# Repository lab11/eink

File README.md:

# E-Ink
This is a BLE-controlled e-ink display built off of the nrf51822.

## Software
The nrf software can be found in ``` /software/nrf5x-base/apps/eink-advanced/ ```

## Summon App
[Summon](https://github.com/lab11/summon) is a UI application for BLE devices. Rather than requiring every user to install a new app for every BLE device, Summon allows BLE devices to point to their own HTML/JS based interface and loads it in a single application. Eink supports the summon architecture and provides a Summon application.

## Hardware
The hardware is built on top of the nrf51822. A full parts list can be found in the ``` /hardware ``` directory, along with pcb and case designs.

## API

| Characteristic name | uuid                                 | Data Type                      | Range   |
| ------------------- | ------------------------------------ | ------------------------------ | --------
| service             | e528a44a-ff4f-3089-d44f-7cb505aba641 | None                           |         |
| text                | e528a410-ff4f-3089-d44f-7cb505aba641 | 20 byte packets up to 60 bytes |         |
| x coordinate        | e528a411-ff4f-3089-d44f-7cb505aba641 | uint16_t                       | 0 - 400 |
| y coordinate        | e528a412-ff4f-3089-d44f-7cb505aba641 | uint16_t                       | 0 - 300 |
| scale               | e528a413-ff4f-3089-d44f-7cb505aba641 | uint8_t                        | 0 - 10  |
| qrcode              | e528a414-ff4f-3089-d44f-7cb505aba641 | 20 bytes                       |         |
| control             | e528a415-ff4f-3089-d44f-7cb505aba641 | uint8_t                        |         |

#### Text
~~1. Break your text up into 19-byte packets.
2. Create an array of these packets.
3. For each packet, make the first byte equal to its distance from the last packet (the first byte of the first packet would be chunks.length - 1, the first byte of the last packet will be 0).
4. The remaining bytes will be the text packet.~~

**You can only write 18 characters at a time.**

#### Control
Writing 1 to control will refresh the display to show changes that have been made.
Writing 2 to control will clear the screen.

### Example

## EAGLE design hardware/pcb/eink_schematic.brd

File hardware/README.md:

#Parts

| Name            | Price  | Link                                                                                                                |
| --------------- | ------ | ------------------------------------------------------------------------------------------------------------------- |
| Eink Display    | $66.00 | http://www.digikey.com/product-detail/en/ST044AS182/ST044AS182-ND/4898786                                           |
| Female headers  | $00.94 | http://www.digikey.com/product-detail/en/sullins-connector-solutions/PPTC101LGBN-RC/S5446-ND/775904                 |
| Inductor        | $00.48 | http://www.digikey.com/product-detail/en/murata-electronics-north-america/LQH43CN100K03L/490-2519-1-ND/599992       |
| 10uF capacitor  | $00.12 | http://www.digikey.com/product-detail/en/murata-electronics-north-america/GRM155R60G106ME44D/490-10693-1-ND/5251412 |
| 2.2uf capacitor | $00.12 | http://www.digikey.com/product-detail/en/murata-electronics-north-america/GRM188R61C225KE15D/490-3296-1-ND/702837   |
| Max6326         | $03.11 | http://www.digikey.com/product-detail/en/maxim-integrated/MAX6326UR29-T/MAX6326UR29-TCT-ND/2234432                  |
| Mosfet          | $00.39 | http://www.digikey.com/product-detail/en/fairchild-semiconductor/FDN340P/FDN340PCT-ND/965604                        |
| Diode           | $00.38 | http://www.digikey.com/product-detail/en/fairchild-semiconductor/SS15FA/SS15FACT-ND/5892131                         |
| Barrel Jack     | $01.89 | http://www.digikey.com/product-detail/en/cui-inc/PJ-002AH-SMT-TR/CP-002AHPJCT-ND/669692                             |

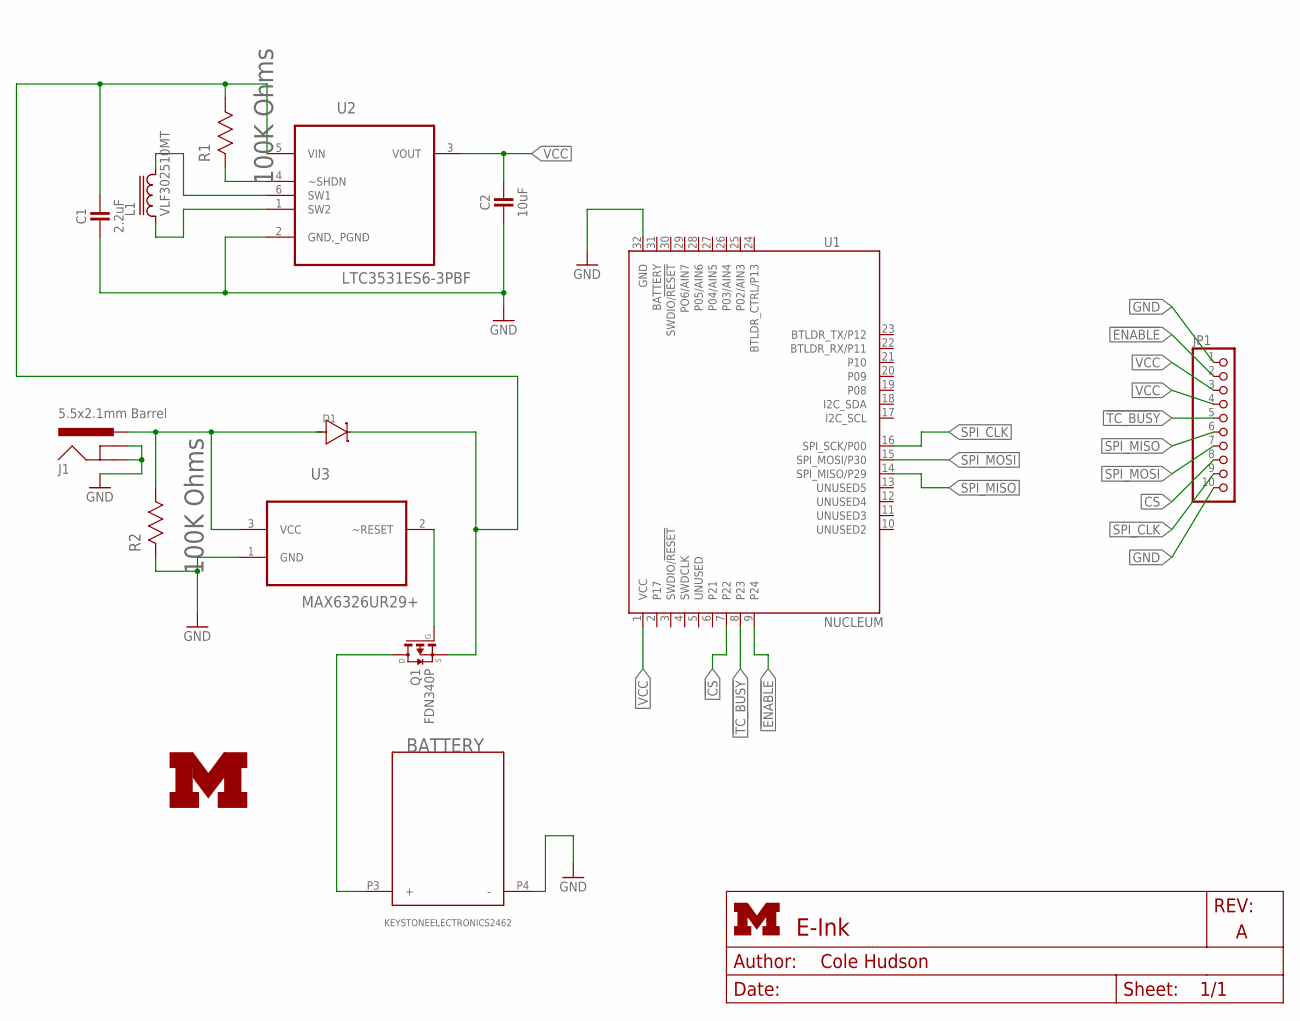
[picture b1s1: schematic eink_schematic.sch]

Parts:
BATTERY: KEYSTONEELECTRONICS2462; DIGIKEY 36-2462-ND
C1: 2.2uF; 0402_CAP; DIGIKEY 490-3296-1-ND
C2: 10uF; 0402_CAP; DIGIKEY 490-10693-1-ND
D1: DIODE[SCHOTKY]-SOD123W; SOD123W; DIGIKEY SS15FACT-ND
J1: 5.5x2.1mm Barrel; POWER_JACK_SMD; DIGIKEY CP-002AHPJCT-ND
JP1: PINHD-1X10/90; 1X10/90; DIGIKEY S5446-ND
L1: VLF302510MT; DIGIKEY 445-6775-1-ND
LOGO1: UMICH_SOLID_LARGE; UMICH_SOLID_350MIL
Q1: FDN340P; SSOT-3; DIGIKEY FDN340PCT-ND
R1: 100K Ohms; RESC1608X60N; DIGIKEY 311-100KGRCT-ND
R2: 100K Ohms; RESC1608X60N
U1: NUCLEUM
U2: LTC3531ES6-3PBF; SOT95P280X100-6N; DIGIKEY LTC3531ES6-3.3#TRMPBFCT-ND
U3: MAX6326UR29+; SOT95P228X119-3N; DIGIKEY MAX6326UR29+TCT-ND

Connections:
!CS: JP1.8, U1.7 (P22)
!ENABLE: JP1.2, U1.9 (P24)
!SHDN: R1.2 (R2), U2.4 (~SHDN)
!TC_BUSY: JP1.5, U1.8 (P23)
GND: BATTERY.P4 (-), C1.2, C2.2, J1.GND (GNDBREAK), J1.P$4 (GND), JP1.1, JP1.10, R2.2 (R2), U1.32 (GND), U2.2 (GND,_PGND), U3.1 (GND)
unnamed: Q1.1 (G), U3.2 (~RESET)
unnamed: D1.P$1 (1), J1.VIN0 (PWR), R2.1 (R1), U3.3 (VCC)
unnamed: C1.1, D1.P$2 (2), Q1.2 (S), R1.1 (R1), U2.5 (VIN)
unnamed: BATTERY.P3 (+), Q1.3 (D)
SPI_CLK: JP1.9, U1.16 (SPI_SCK/P00)
SPI_MISO: JP1.6, U1.14 (SPI_MISO/P29)
SPI_MOSI: JP1.7, U1.15 (SPI_MOSI/P30)
SW1: L1.2, U2.6 (SW1)
SW2: L1.1, U2.1 (SW2)
VCC: C2.1, JP1.3, JP1.4, U1.1 (VCC), U2.3 (VOUT)

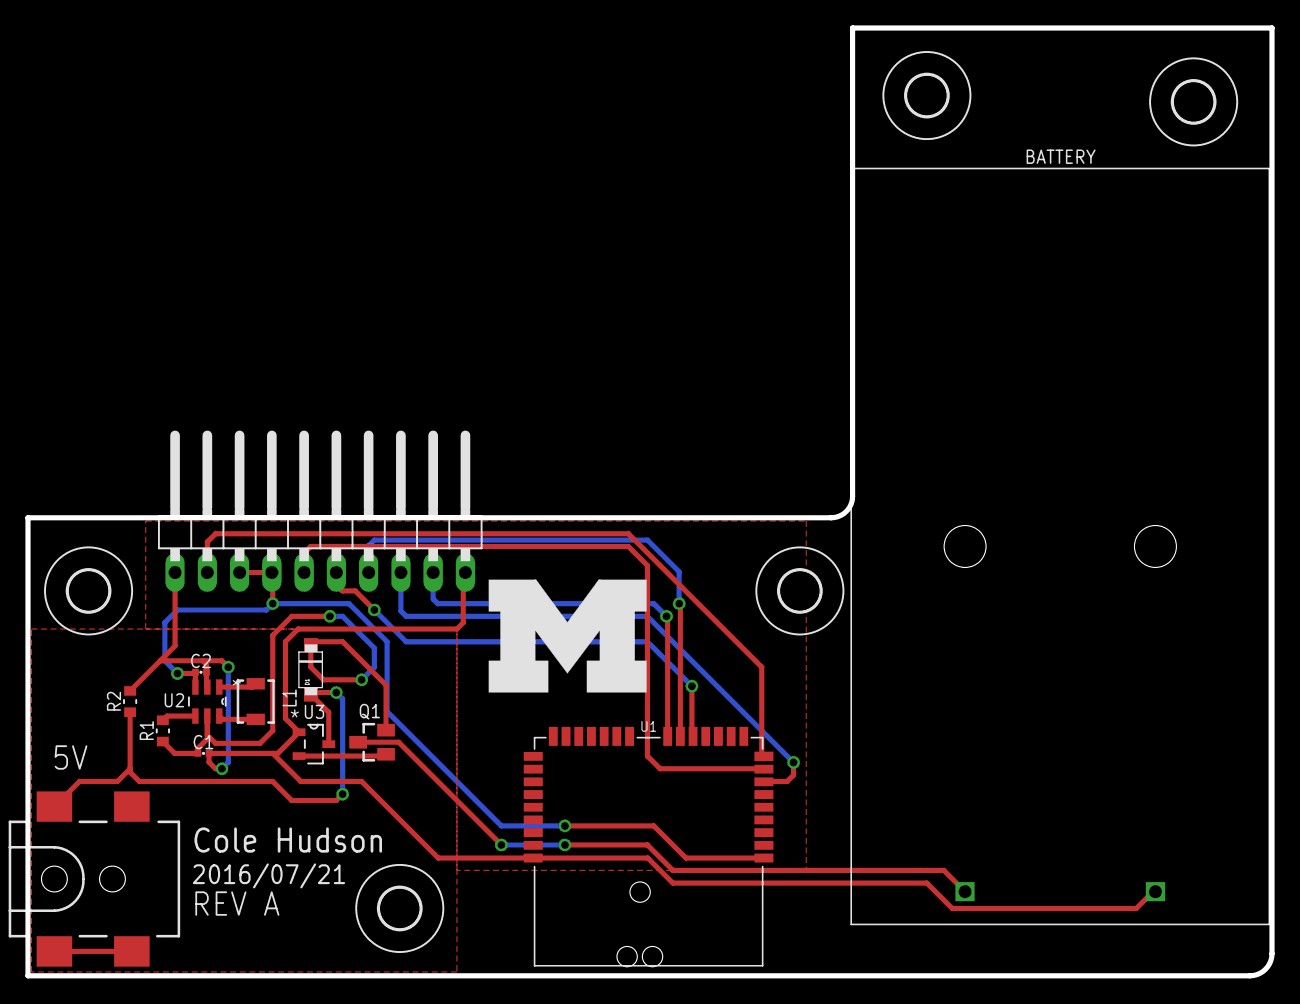
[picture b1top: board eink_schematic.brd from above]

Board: 2 copper layers, 97.9 x 74.6 mm, 19 parts (0 on the bottom side), 15 nets.

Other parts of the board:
U$1, U$2, U$3, U$4, U$5: 3,2

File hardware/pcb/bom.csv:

Qty,Value,Device,Package,Parts,Description,DIGIKEY,MPN,OC_FARNELL,OC_NEWARK,PACKAGE,PROD_ID,SF_ID,SUPPLIER,TOLERANCE,VALUE,WATTAGE
1,,DIODE[SCHOTKY]-SOD123W,SOD123W,D1,,SS15FACT-ND,,,,,,,,,,
1,,PINHD-1X10/90,1X10/90,JP1,PIN HEADER,S5446-ND,,,,,,,,,,
1,100K Ohms,RC0603JR-07100KL,RESC1608X60N,R1,"RESISTOR, 0603",311-100KGRCT-ND,RC0603JR-07100KL,9233628,98K7287,,,,Yageo,±5%,100K Ohms,1/10 W
1,100K Ohms,RC0603JR-07100KL,RESC1608X60N,R2,"RESISTOR, 0603",,RC0603JR-07100KL,9233628,98K7287,,,,Yageo,±5%,100K Ohms,1/10 W
1,10uF,CAPACITOR,0402_CAP,C2,0402 Capacitor,490-10693-1-ND,,,,,,,,,,
1,2.2uF,CAPACITOR,0402_CAP,C1,0402 Capacitor,490-3296-1-ND,,,,,,,,,,
1,5.5x2.1mm Barrel,POWER_JACKSMD,POWER_JACK_SMD,J1,Power Jack,CP-002AHPJCT-ND,,,,,CONN-08106,PRT-12748,,,5.5x2.1mm Barrel,
1,FDN340P,FDN340P,SSOT-3,Q1,P-Channel MOSFET,FDN340PCT-ND,,,,,,,,,,
1,KEYSTONEELECTRONICS2462,KEYSTONEELECTRONICS2462,KEYSTONEELECTRONICS2462,BATTERY,,36-2462-ND,,,,,,,,,,
1,LTC3531ES6-3PBF,LTC3531ES6-3PBF,SOT95P280X100-6N,U2,DC/DC Converters,LTC3531ES6-3.3#TRMPBFCT-ND,LTC3531ES6-3#PBF,-,46P4583,TSOT-23-6,,,Linear Technology,,,
1,MAX6326UR29+,MAX6326UR29+,SOT95P228X119-3N,U3,"3-Pin, Ultra-Low-Power SC70/SOT ìP Reset Circuits",MAX6326UR29+TCT-ND,MAX6326UR29+,9723951,-,SOT-23-3,,,Maxim,,,
1,NUCLEUM,NUCLEUM,NUCLEUM,U1,Nucleum sensorboard prototyping module.,,,,,,,,,,,
1,UMICH_SOLID_LARGE,UMICH_SOLID_LARGE,UMICH_SOLID_350MIL,LOGO1,,,,,,,,,,,,
1,VLF302510MT,VLF302510MT,VLF302510MT,L1,POWER INDUCTOR,445-6775-1-ND,,,,,,,,,,

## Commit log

2016-06-28 Added base summon app
2016-06-28 Added nrf5x-base submodule
2016-06-29 Added readme for summon
2016-06-29 Hopefully fixed summon readme
2016-06-29 added previous bletestsite
2016-06-29 Switched to cordova stuff and then reverted back
2016-06-29 console.log instead of app.log
2016-06-29 test console.log
2016-06-29 switched to old bluetooth file
2016-06-29 rev10 old bluetooth
2016-06-29 Content security policy
2016-06-29 Hopefully fixed content security policy
2016-06-29 rev12
2016-06-29 Moved libraries to be local so it doesn't violate the CSP
2016-06-29 rev13
2016-06-29 No longer tries to set deviceid in html
2016-06-29 rev14
2016-06-29 line 48 index.js causing trouble
2016-06-29 rev16: added cordova stuff
2016-06-29 rev17: attempt to connect to device
2016-06-29 Attempt bluetooth write
2016-06-29 rev19: string to array buffer maybe working now
2016-06-29 console.log on bluetooth write
2016-06-29 rev20 use ble lib directly instead of bluetooth
2016-06-29 rev21: actually send data lol
2016-06-29 rev23: try different write address
2016-06-29 rev24: hyphenated addresses
2016-06-29 rev25: write without response
2016-06-29 rev26: log error on write
2016-06-30 rev27: cordova plugins
2016-06-30 rev 28: added the plugins folder
2016-06-30 rev29: switched back to normal write
2016-06-30 rev30: stringtobytes
2016-06-30 rev31: onclick
2016-06-30 rev32: onclick hopefully better
2016-06-30 rev33: write value from text box
2016-06-30 rev34: default input values
2016-06-30 default input values should work now
2016-06-30 rev36: attempt to write x, y, and scale
2016-06-30 rev37: no longer try to write(x, y) and scale.
2016-06-30 rev38: only write on click.
2016-06-30 rev39: modified writeText()
2016-06-30 rev40: loop write
2016-06-30 rev41: Callbacks for successive writes.
2016-06-30 rev42: fixed capitalization error in index.js@line115
2016-06-30 rev43: writeBufferAttempts now defined
2016-06-30 rev44: writeBufferAttempts corrected
2016-06-30 rev45: writeBufferAttempts should now be fixed
2016-06-30 rev46: Write without response
2016-06-30 rev47: fixed params on callbacks
2016-06-30 rev48: log device and attached characteristics
2016-07-01 rev49: modified stringify
2016-07-01 rev50: alternate characteristic uuid format
2016-07-01 rev51: write with response
2016-07-01 rev52: print characteristics after successful connection
2016-07-01 rev53: connect to different device
2016-07-01 rev54: replaced deviceId with bleAddress
2016-07-01 rev55: different char address form
2016-07-01 rev56: Changed in response to github issue I created. Thanks @Don Coleman
2016-07-01 rev56: changes in response to github issue
2016-07-01 rev57: set char uuids to printout from previous run
2016-07-01 rev58: switched back to normal write @Don Coleman
2016-07-02 rev58
2016-07-02 rev59: removed stringToBytes on numbers
2016-07-02 rev60: console.log error with rev#
2016-07-02 Created eagle project + schematic
2016-07-05 rev61: parseInt on 3/5 characteristics
2016-07-05 rev62: log char uuid on fail
2016-07-05 rev53: buffer byte length
2016-07-05 reg64: removed extra buffer creation
2016-07-05 rev65: stringToBytes on x coord
2016-07-05 reg66: long to byte array from stack overflow
2016-07-05 rev67: int string to bytes
2016-07-05 rev 68: removed long to bytes function
2016-07-05 rev69: console.log on callback
2016-07-05 rev70: disconnect from device after successful write
2016-07-05 rev71: console.log on scan and connect attempts + scan error
2016-07-05 rev72: callback on disconnect success
2016-07-06 rev73: test just writing text
2016-07-06 rev74: https://github.com/don/cordova-plugin-ble-central/issues/270#issuecomment-230790264
2016-07-06 rev75: log the buffer being written
2016-07-06 rev76: try to CORRECTLY log the x coordinate buffer
2016-07-06 rev77: convert uint8 array to ArrayBuffer
2016-07-12 rev78: just try writing text
2016-07-12 rev79: callback is a function for writeText
2016-07-13 rev80: switched to using rawgit cdn
2016-07-13 rev81: switched back to trying to write everything in succession, not just text
2016-07-13 rev82: print scan number
2016-07-13 rev83: 5 second timeout on scan
2016-07-13 rev84: removed writeScans++ error
2016-07-13 rev85: don't disconnect from device between writes
2016-07-13 added eink icon
2016-07-13 rev86: icon working maybe
2016-07-13 rev87: icon should work for real now
2016-07-13 rev88: icon still won't work :(
2016-07-13 rev89: added callback back in
2016-07-13 rev90: disconnect after successful write
2016-07-13 rev91: disconnect from device.id, not device
2016-07-13 rev92: wroteSuccessfully = false before each write
2016-07-13 rev93: disconnect on click if connected
2016-07-13 rev94: qr code connect before other stuff
2016-07-13 rev95: qr code callback disconnect
2016-07-13 rev96: stop checking for wrotesSuccessfully
2016-07-13 rev97: no more conditions on connections/scanning
2016-07-13 rev98: no more conditions on writing
2016-07-13 rev99: added null character to strings
2016-07-13 added labels for bounds
2016-07-14 rev100: limit range of numbers and size of strings
2016-07-14 rev101: fixed substring
2016-07-14 rev102: multiple disconnect attempts
2016-07-14 rev103: previous rang limiters weren't working
2016-07-14 rev104: moved labels
2016-07-14 rev105: labels on same line
2016-07-14 rev106: removed disconnect loop
2016-07-14 rev107: substring of strings to keep in range
2016-07-14 rev108: disconnect after each write
2016-07-14 rev109: increased scan timeout to 10 seconds
2016-07-14 rev110: check if connected before a write
2016-07-14 rev111: console.log to debug connection issues
2016-07-14 rev112: switched back to staying connected
2016-07-14 rev113: json.stringify connection error
2016-07-14 rev114: json.stringify THE CORRECT connection error
2016-07-14 updated index.html to rev114
2016-07-14 rev115: disconnect callback
2016-07-14 rev116: 16 bit numbers sent in Uint16array, not Uint8array
2016-07-14 rev117: scale is still 8 bit
2016-07-14 rev118: scale slider
2016-07-14 rev119: scale slider get value correctly
2016-07-14 rev120: scale slider get value correctly
2016-07-14 rev121: no longer call parseInt on the int from the slider
2016-07-14 rev122: capitalization error fixed on jquery scaleInput selector
2016-07-14 rev123: table for input
2016-07-14 rev124: shortened labels
2016-07-15 rev125: added control characteristic for screen update and clear
2016-07-15 rev126: fixed controlUuid spelling error
2016-07-15 rev127: label clear screen slider + qr code set control in callback
2016-07-15 rev128: removed references to globalDevice and device
2016-07-15 rev129: removed reference to device in writeBuffer failure
2016-07-15 rev130: shortened length of text
2016-07-15 rev131: send strings in 20 byte chunks
2016-07-15 rev132: console.logs to debug
2016-07-15 rev133: console.log chunks
2016-07-15 rev134: removed space after comma in regex
2016-07-15 rev135: replaced string with text
2016-07-15 rev136: console.log chunk to be sent
2016-07-15 rev137: all chunks same length
2016-07-15 rev138: split by 19
2016-07-15 rev139: switched back to splitting by 18
2016-07-15 rev140: compare to chunks.length, not 0
2016-07-15 rev141: no longer add null character after string
2016-07-15 rev142: make sure chunk isn't undefined
2016-07-16 rev143: added control to write text to the screen array
2016-07-16 rev144: removed control to write text to the screen array
2016-07-18 rev145: Text index count down to 0
2016-07-18 rev146: chunks.length - 1 instead of chunks.length to stay within bounds
2016-07-19 Added link to female header in README
2016-07-19 Eagle: labeled B3-5 and SPI pins
2016-07-19 Added parts list
2016-07-19 fixed readme
2016-07-19 Added software description for readme
2016-07-19 Added api description to communicate with the display
2016-07-19 API: corrected packet length
2016-07-19 Clarified software in readme
2016-07-19 Eagle: Added headers and labeled more
2016-07-19 Added range values in readme
2016-07-19 You can only write 18 characters at a time
2016-07-19 rev147: okay. you can only write 18 characters at a time
2016-07-19 rev148: null character after text
2016-07-19 added buck/boost regulator to schematic
2016-07-20 Added some libs, buck/boost regulator, and barrel jack
2016-07-20 Created L-shaped board
2016-07-20 added digikey part numbers for everything
2016-07-20 Eagle: pretty sure I got things wired up
2016-07-21 deleted traces from 1st try
2016-07-21 Traces try #2 looks much better
2016-07-21 Corrected spacing
2016-07-21 centered board on origin and added measurements
2016-07-21 re-wired and created eagle part for through-hole battery pack
2016-07-22 wiring is good + added GND plane
2016-07-22 Measurements all check out
2016-07-22 redid battery
2016-07-22 generated gerbers and re-numbered
2016-07-22 started running brad's python scripts
2016-07-22 Submitted order
2016-07-26 the pcbs were ordered
2016-07-26 started designing case
2016-07-26 added screen dimensions and wall dimensions
2016-07-26 tried printing a corner. DON'T DO OVERHANGS
2016-07-27 Added screw holes
2016-07-27 Added back of case
2016-07-27 Started adding screw holes to the case back
2016-07-27 front and back holes to connect
2016-07-27 Added chamfered holes
2016-07-28 started adding mounting points for pcb
2016-07-28 Added mounting points for the pcb and extruded
2016-07-28 Added extrusion to hold display in place from the back
2016-07-28 Added 6mm edge fillet
2016-07-28 Added noble app. Connect and get occupancy value
2016-07-28 Started printing case. Generated STLs
2016-07-28 reads occupancy and updates display accordingly
2016-07-28 Scales text correctly
2016-07-28 turn display on and off over ble
2016-07-28 fixed font8x8 submodule issue
2016-07-28 display text sent over bluetooth
2016-07-28 cleaned up code
2016-07-28 generates and prints qr codes
2016-07-28 write text @ (x,y) + scale + qrcode over ble. Added send_ble_data.js
2016-07-28 Turn on and off individual pixels
2016-07-28 hopefully fixed nrf_gpio_pin_clear(nTC_EN) issue
2016-07-28 Write string of text at exact pixel location
2016-07-28 Deleted .ds_store
2016-07-28 Scale graphics
2016-07-28 The pixel change function is much more precise
2016-07-28 Now writes long strings of characters
2016-07-28 Add grid of pixels to image
2016-07-28 Combined eink-advanced with service-example. Turning the led on also activates the eink display
2016-07-28 Displays 21x21 qr code
2016-07-28 created function to edit picture at (x,y)
2016-07-28 removed a special folder causing problems
2016-07-28 Added font and properly prints characters
2016-07-28 Added in nrf code from nrf5x-base repo
2016-07-29 Fixed diameter/radius problems (hopefully)
2016-07-29 Removed cordova app
2016-07-29 Updated to use the tcmp441 lib
2016-07-29 removed build folder
2016-07-29 moved libqrencode to nrf5x-base
2016-07-29 updated to use control char
2016-07-29 removed __STATIC
2016-07-29 Added gitignore for _build
2016-07-29 removed _build
2016-07-30 removed ~$ stuff
2016-08-03 Added hole for barrel jack
2016-08-03 fillet hole for barrel jack
2016-08-04 converted pegs into screw-mounting holes
2016-08-04 fillet on those screw holes
2016-08-04 Started TerraSwarm report
2016-08-04 Started printing case after most recent changes
2016-08-04 report v0
2016-08-04 Added fillet on top part of case for the connecting pegs
2016-08-08 Added extruded piece to hold display in place
2016-08-08 moved display holder off to the side to avoid ribbon cable
2016-08-09 added top brackets for display and fixed fillet on bottom corners
2016-08-11 improved case
2016-08-12 write all values from occupancy.js
2016-08-12 error on connect. Command disallowed
2016-08-12 occupancy-eink.js: IT WORKS!

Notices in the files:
parts and their libraries:
SparkFun-Connectors: Licensing: Creative Commons ShareAlike 4.0 International - https://creativecommons.org/licenses/by-sa/4.0
inductor-tdk: Copyright (C) 2008, Bob Starr
